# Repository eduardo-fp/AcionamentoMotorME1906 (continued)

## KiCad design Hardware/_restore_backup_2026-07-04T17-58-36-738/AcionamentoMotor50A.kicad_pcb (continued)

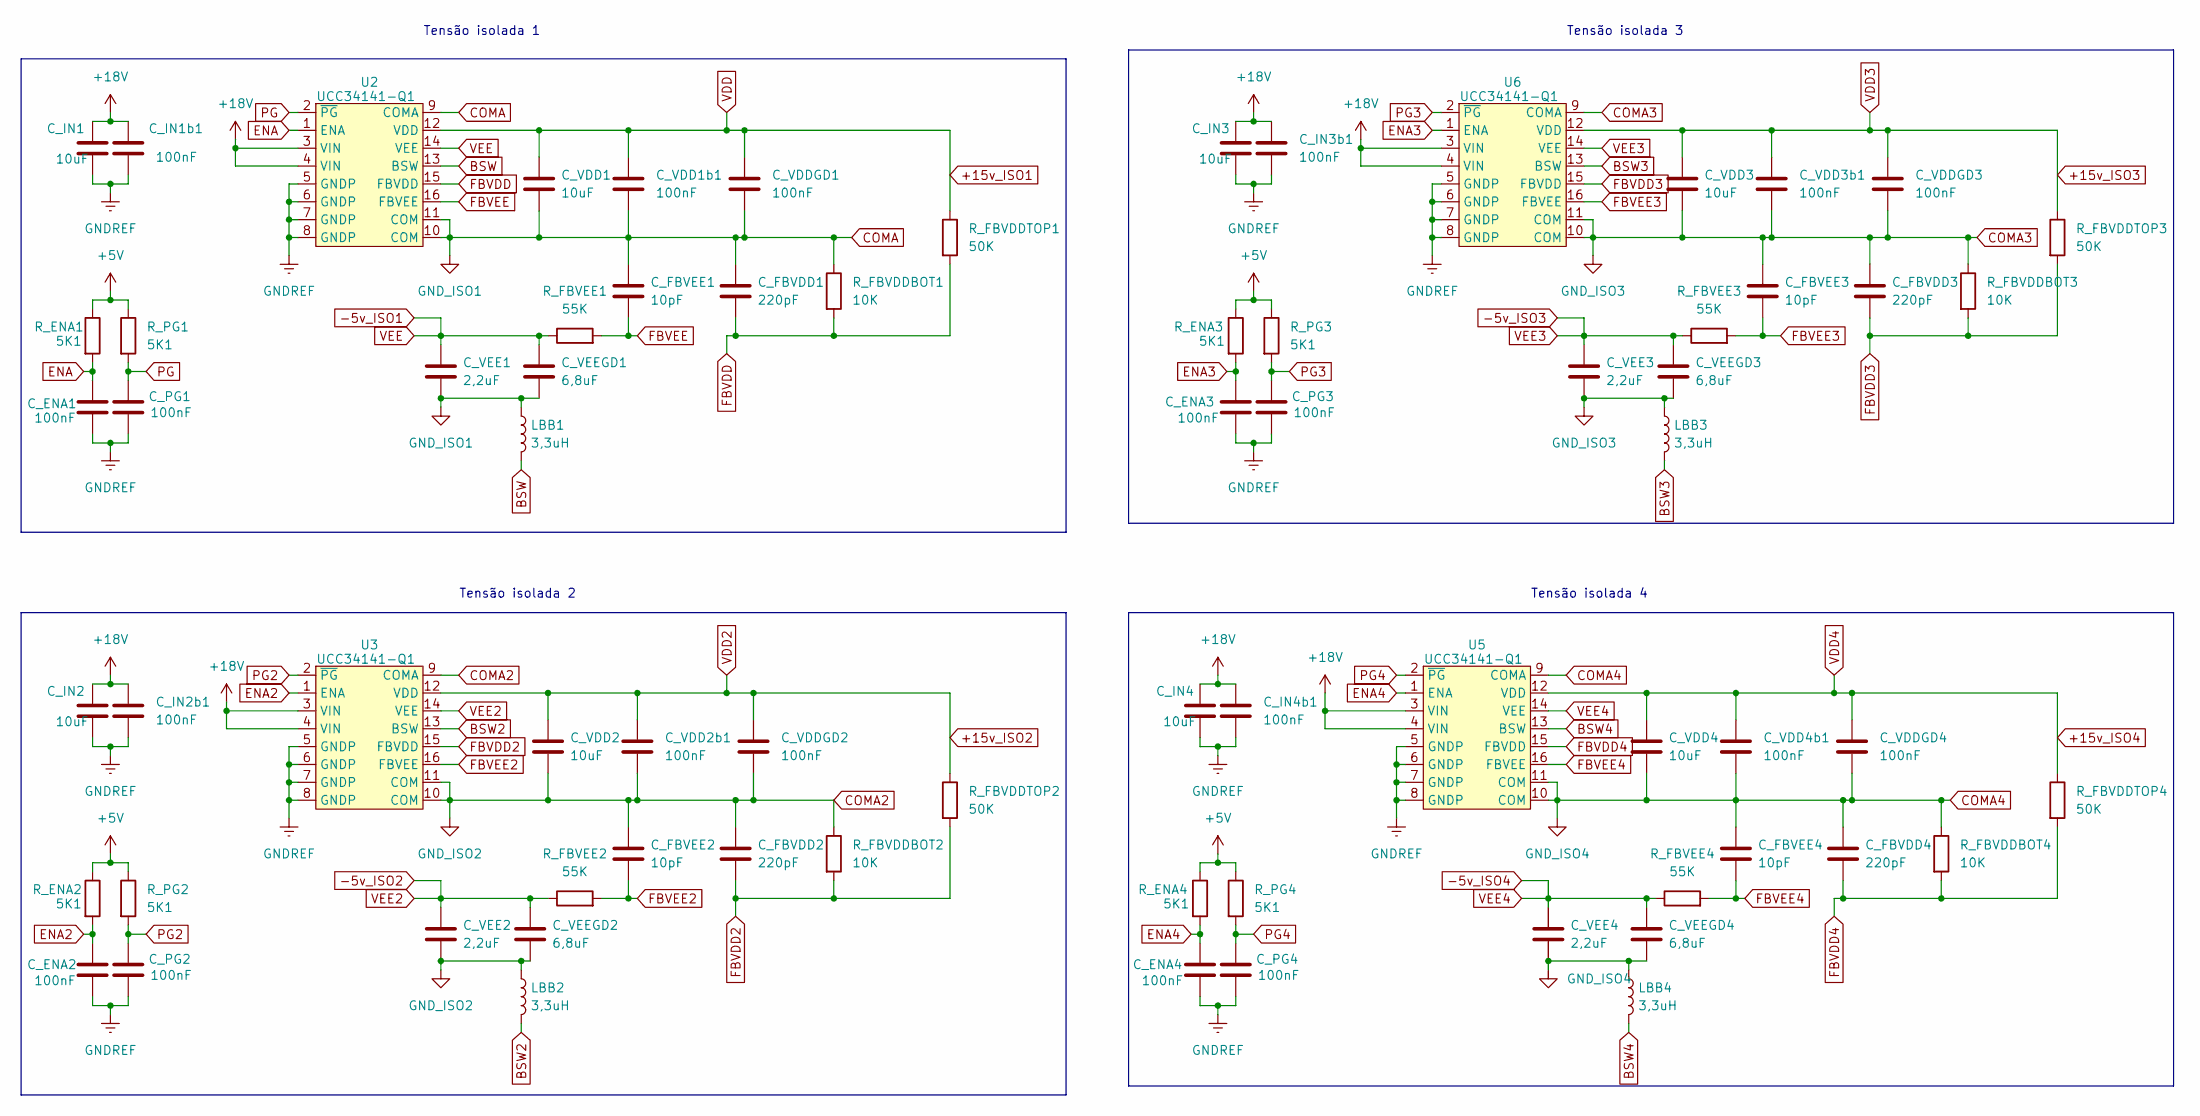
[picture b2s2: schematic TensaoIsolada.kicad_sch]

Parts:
C_ENA1, C_ENA2, C_ENA3, C_ENA4: 100nF; C_0805_2012Metric_Pad1.18x1.45mm_HandSolder
C_FBVDD1, C_FBVDD2, C_FBVDD3, C_FBVDD4: 220pF; C_0805_2012Metric_Pad1.18x1.45mm_HandSolder
C_FBVEE1, C_FBVEE2, C_FBVEE3, C_FBVEE4: 10pF; C_0805_2012Metric_Pad1.18x1.45mm_HandSolder
C_IN1, C_IN2, C_IN3, C_IN4: 10uF; C_0805_2012Metric_Pad1.18x1.45mm_HandSolder
C_IN1b1, C_IN2b1, C_IN3b1, C_IN4b1: 100nF; C_0805_2012Metric_Pad1.18x1.45mm_HandSolder
C_PG1, C_PG2, C_PG3, C_PG4: 100nF; C_0805_2012Metric_Pad1.18x1.45mm_HandSolder
C_VDD1, C_VDD2, C_VDD3, C_VDD4: 10uF; C_0805_2012Metric_Pad1.18x1.45mm_HandSolder
C_VDD1b1, C_VDD2b1, C_VDD3b1, C_VDD4b1: 100nF; C_0805_2012Metric_Pad1.18x1.45mm_HandSolder
C_VDDGD1, C_VDDGD2, C_VDDGD3, C_VDDGD4: 100nF; C_0805_2012Metric_Pad1.18x1.45mm_HandSolder
C_VEE1, C_VEE2, C_VEE3, C_VEE4: 2,2uF; C_0805_2012Metric_Pad1.18x1.45mm_HandSolder
C_VEEGD1, C_VEEGD2, C_VEEGD3, C_VEEGD4: 6,8uF; C_0805_2012Metric_Pad1.18x1.45mm_HandSolder
LBB1, LBB2, LBB3, LBB4: 3,3uH; L_0805_2012Metric_Pad1.05x1.20mm_HandSolder
R_ENA1, R_ENA2, R_ENA3, R_ENA4: 5K1; R_0805_2012Metric_Pad1.20x1.40mm_HandSolder
R_FBVDDBOT1, R_FBVDDBOT2, R_FBVDDBOT3, R_FBVDDBOT4: 10K; R_0805_2012Metric_Pad1.20x1.40mm_HandSolder
R_FBVDDTOP1, R_FBVDDTOP2, R_FBVDDTOP3, R_FBVDDTOP4: 50K; R_0805_2012Metric_Pad1.20x1.40mm_HandSolder
R_FBVEE1, R_FBVEE2, R_FBVEE3, R_FBVEE4: 55K; R_0805_2012Metric_Pad1.20x1.40mm_HandSolder
R_PG1, R_PG2, R_PG3, R_PG4: 5K1; R_0805_2012Metric_Pad1.20x1.40mm_HandSolder
U2, U3, U5, U6: UCC34141-Q1; SSOP-16_4.55x10.63mm_P0.65mm

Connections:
+5V: R_ENA1.1, R_ENA2.1, R_ENA3.1, R_ENA4.1, R_PG1.1, R_PG2.1, R_PG3.1, R_PG4.1; also elsewhere on the board
+15v_ISO1: C_VDD1.1, C_VDD1b1.1, C_VDDGD1.1, R_FBVDDTOP1.1, U2.12 (VDD)
+15v_ISO2: C_VDD2.1, C_VDD2b1.1, C_VDDGD2.1, R_FBVDDTOP2.1, U3.12 (VDD)
+15v_ISO3: C_VDD3.1, C_VDD3b1.1, C_VDDGD3.1, R_FBVDDTOP3.1, U6.12 (VDD)
+15v_ISO4: C_VDD4.1, C_VDD4b1.1, C_VDDGD4.1, R_FBVDDTOP4.1, U5.12 (VDD)
+18V: C_IN1.1, C_IN1b1.1, C_IN2.1, C_IN2b1.1, C_IN3.1, C_IN3b1.1, C_IN4.1, C_IN4b1.1, U2.3 (VIN), U2.4 (VIN), U3.3 (VIN), U3.4 (VIN), U5.3 (VIN), U5.4 (VIN), U6.3 (VIN), U6.4 (VIN); also elsewhere on the board
-5v_ISO1: C_VEE1.1, C_VEEGD1.1, R_FBVEE1.1, U2.14 (VEE)
-5v_ISO2: C_VEE2.1, C_VEEGD2.1, R_FBVEE2.1, U3.14 (VEE)
-5v_ISO3: C_VEE3.1, C_VEEGD3.1, R_FBVEE3.1, U6.14 (VEE)
-5v_ISO4: C_VEE4.1, C_VEEGD4.1, R_FBVEE4.1, U5.14 (VEE)
BAT-: C_ENA1.2, C_ENA2.2, C_ENA3.2, C_ENA4.2, C_IN1.2, C_IN1b1.2, C_IN2.2, C_IN2b1.2, C_IN3.2, C_IN3b1.2, C_IN4.2, C_IN4b1.2, C_PG1.2, C_PG2.2, C_PG3.2, C_PG4.2, U2.5 (GNDP), U2.6 (GNDP), U2.7 (GNDP), U2.8 (GNDP), U3.5 (GNDP), U3.6 (GNDP), U3.7 (GNDP), U3.8 (GNDP), U5.5 (GNDP), U5.6 (GNDP), U5.7 (GNDP), U5.8 (GNDP), U6.5 (GNDP), U6.6 (GNDP), U6.7 (GNDP), U6.8 (GNDP); also elsewhere on the board
BSW: LBB1.2, U2.13 (BSW)
BSW2: LBB2.2, U3.13 (BSW)
BSW3: LBB3.2, U6.13 (BSW)
BSW4: LBB4.2, U5.13 (BSW)
COMA: C_FBVDD1.1, C_FBVEE1.1, C_VDD1.2, C_VDD1b1.2, C_VDDGD1.2, C_VEE1.2, C_VEEGD1.2, LBB1.1, R_FBVDDBOT1.1, U2.9 (COMA), U2.10 (COM), U2.11 (COM)
COMA2: C_FBVDD2.1, C_FBVEE2.1, C_VDD2.2, C_VDD2b1.2, C_VDDGD2.2, C_VEE2.2, C_VEEGD2.2, LBB2.1, R_FBVDDBOT2.1, U3.9 (COMA), U3.10 (COM), U3.11 (COM)
COMA3: C_FBVDD3.1, C_FBVEE3.1, C_VDD3.2, C_VDD3b1.2, C_VDDGD3.2, C_VEE3.2, C_VEEGD3.2, LBB3.1, R_FBVDDBOT3.1, U6.9 (COMA), U6.10 (COM), U6.11 (COM)
COMA4: C_FBVDD4.1, C_FBVEE4.1, C_VDD4.2, C_VDD4b1.2, C_VDDGD4.2, C_VEE4.2, C_VEEGD4.2, LBB4.1, R_FBVDDBOT4.1, U5.9 (COMA), U5.10 (COM), U5.11 (COM)
ENA: C_ENA1.1, R_ENA1.2, U2.1 (ENA)
ENA2: C_ENA2.1, R_ENA2.2, U3.1 (ENA)
ENA3: C_ENA3.1, R_ENA3.2, U6.1 (ENA)
ENA4: C_ENA4.1, R_ENA4.2, U5.1 (ENA)
FBVDD: C_FBVDD1.2, R_FBVDDBOT1.2, R_FBVDDTOP1.2, U2.15 (FBVDD)
FBVDD2: C_FBVDD2.2, R_FBVDDBOT2.2, R_FBVDDTOP2.2, U3.15 (FBVDD)
FBVDD3: C_FBVDD3.2, R_FBVDDBOT3.2, R_FBVDDTOP3.2, U6.15 (FBVDD)
FBVDD4: C_FBVDD4.2, R_FBVDDBOT4.2, R_FBVDDTOP4.2, U5.15 (FBVDD)
FBVEE: C_FBVEE1.2, R_FBVEE1.2, U2.16 (FBVEE)
FBVEE2: C_FBVEE2.2, R_FBVEE2.2, U3.16 (FBVEE)
FBVEE3: C_FBVEE3.2, R_FBVEE3.2, U6.16 (FBVEE)
FBVEE4: C_FBVEE4.2, R_FBVEE4.2, U5.16 (FBVEE)
PG: C_PG1.1, R_PG1.2, U2.2 (~PG)
PG2: C_PG2.1, R_PG2.2, U3.2 (~PG)
PG3: C_PG3.1, R_PG3.2, U6.2 (~PG)
PG4: C_PG4.1, R_PG4.2, U5.2 (~PG)

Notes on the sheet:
Tensão isolada 4
Tensão isolada 2
Tensão isolada 3
Tensão isolada 1

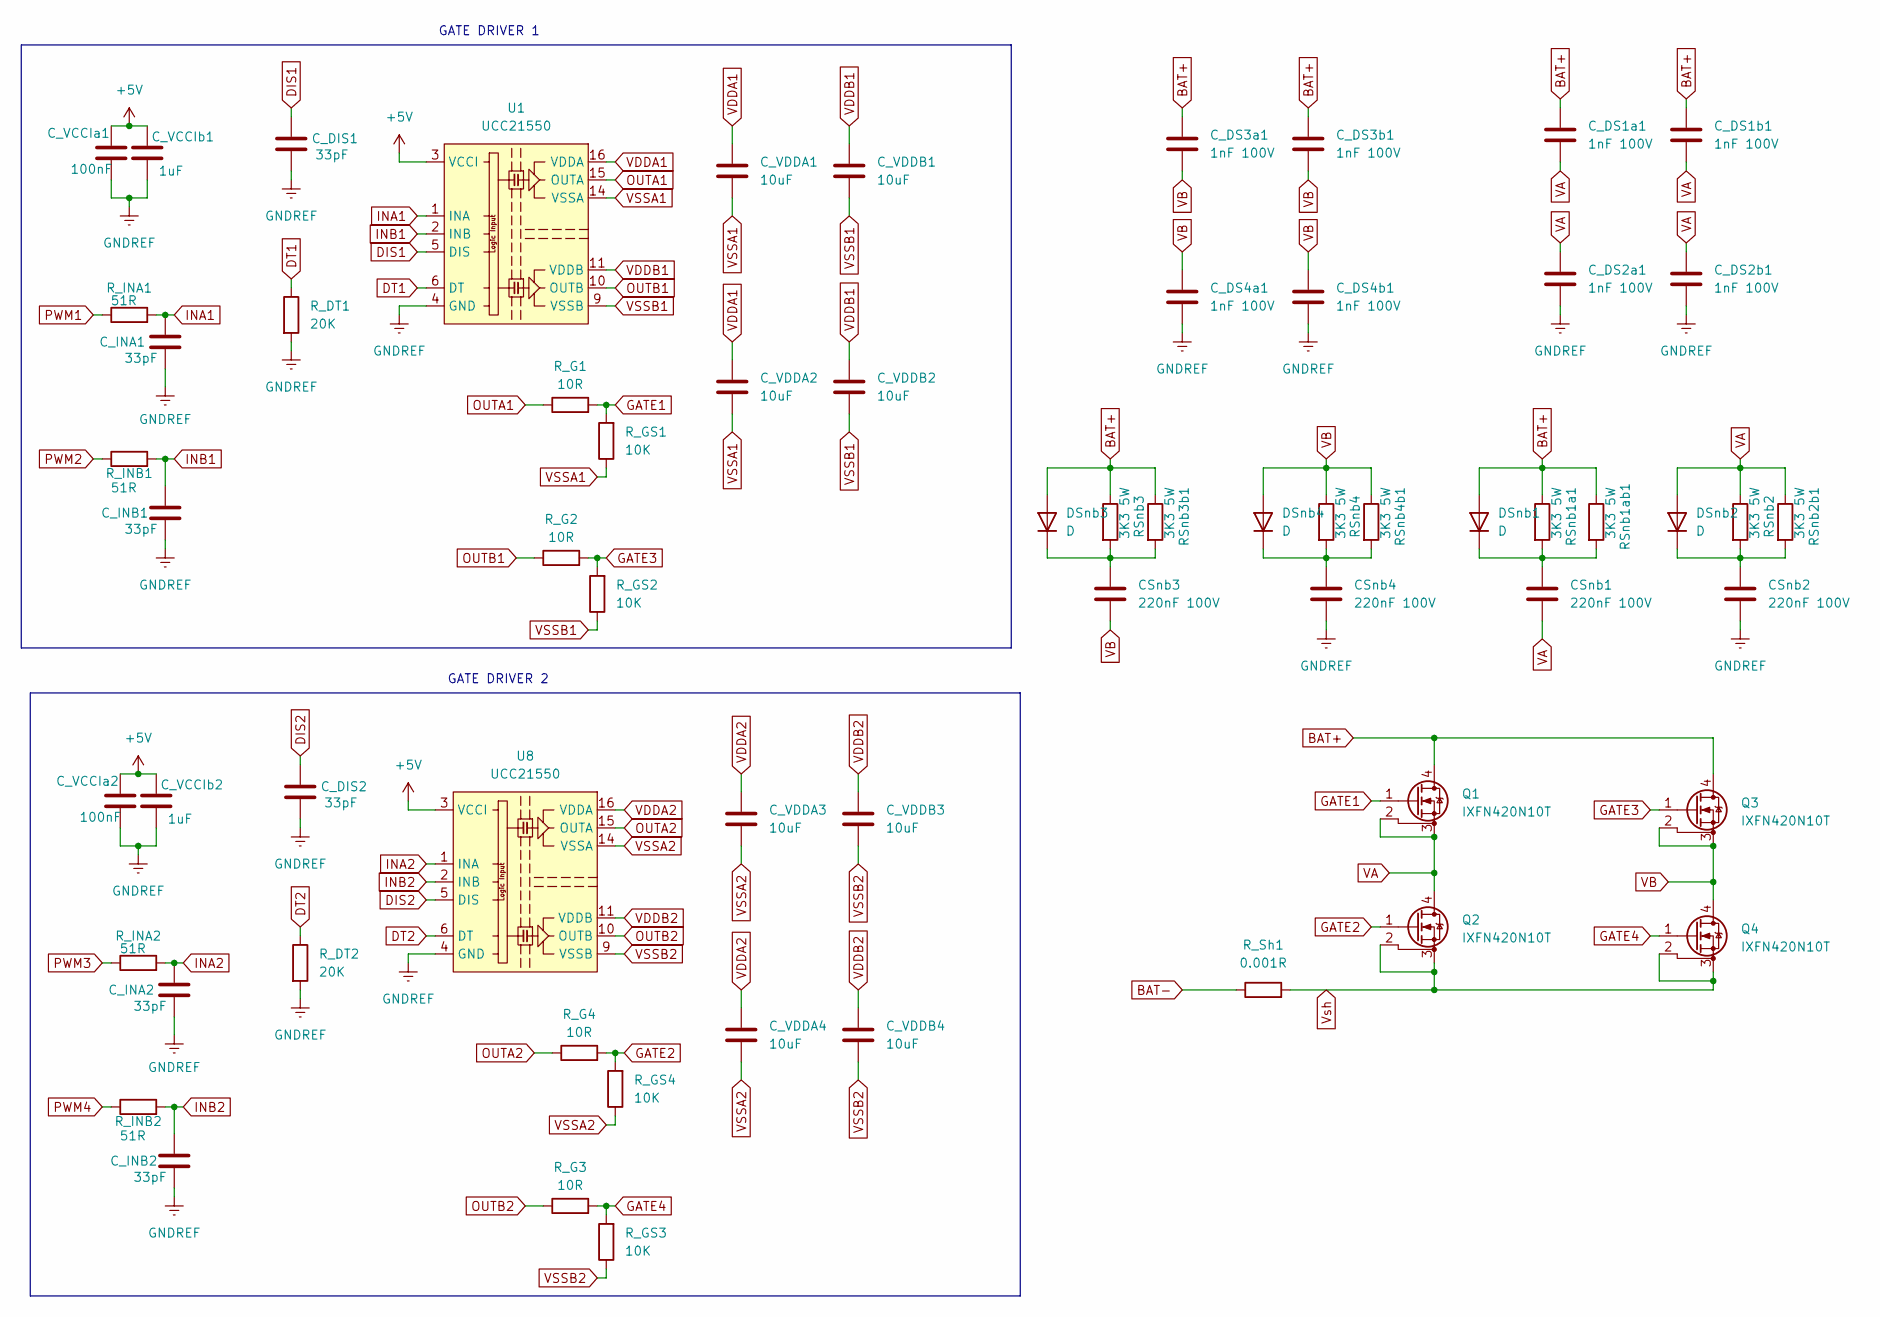
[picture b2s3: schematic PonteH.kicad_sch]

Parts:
CSnb1, CSnb2, CSnb3, CSnb4: 220nF 100V; C_Axial_L5.1mm_D3.1mm_P10.00mm_Horizontal
C_DIS1, C_DIS2: 33pF; C_0805_2012Metric_Pad1.18x1.45mm_HandSolder
C_DS1a1, C_DS1b1, C_DS2a1, C_DS2b1, C_DS3a1, C_DS3b1, C_DS4a1, C_DS4b1: 1nF 100V; C_0805_2012Metric_Pad1.18x1.45mm_HandSolder
C_INA1, C_INA2: 33pF; C_0805_2012Metric_Pad1.18x1.45mm_HandSolder
C_INB1, C_INB2: 33pF; C_0805_2012Metric_Pad1.18x1.45mm_HandSolder
C_VCCI​a1, C_VCCI​a2: 100nF; C_0805_2012Metric_Pad1.18x1.45mm_HandSolder
C_VCCI​b1, C_VCCI​b2: 1uF; C_0805_2012Metric_Pad1.18x1.45mm_HandSolder
C_VDDA1, C_VDDA2, C_VDDA3, C_VDDA4: 10uF; C_0805_2012Metric_Pad1.18x1.45mm_HandSolder
C_VDDB1, C_VDDB2, C_VDDB3, C_VDDB4: 10uF; C_0805_2012Metric_Pad1.18x1.45mm_HandSolder
DSnb1, DSnb2, DSnb3, DSnb4: D; D_SMA_Handsoldering
Q1, Q2, Q3, Q4: IXFN420N10T; SOT-227
RSnb1a1, RSnb1ab1, RSnb2, RSnb2b1, RSnb3, RSnb3b1, RSnb4, RSnb4b1: 3K3 5W; R_Axial_Power_L25.0mm_W9.0mm_P27.94mm
R_DT1, R_DT2: 20K; R_0805_2012Metric_Pad1.20x1.40mm_HandSolder
R_G1, R_G2, R_G3, R_G4: 10R; R_0805_2012Metric_Pad1.20x1.40mm_HandSolder
R_GS1, R_GS2, R_GS3, R_GS4: 10K; R_0805_2012Metric_Pad1.20x1.40mm_HandSolder
R_INA1, R_INA2: 51R; R_0805_2012Metric_Pad1.20x1.40mm_HandSolder
R_INB1, R_INB2: 51R; R_0805_2012Metric_Pad1.20x1.40mm_HandSolder
R_Sh1: 0.001R; R_Axial_Power_L20.0mm_W6.4mm_P25.40mm
U1, U8: UCC21550; SOIC-16W_7.5x10.3mm_P1.27mm

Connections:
+5V: C_VCCI​a1.1, C_VCCI​a2.1, C_VCCI​b1.1, C_VCCI​b2.1, U1.3 (VCCI), U1.8 (VCCI), U8.3 (VCCI), U8.8 (VCCI); also elsewhere on the board
BAT+: C_DS1a1.1, C_DS1b1.1, C_DS3a1.1, C_DS3b1.1, DSnb1.2 (A), DSnb3.2 (A), Q1.4 (D), Q3.4 (D), RSnb1a1.1, RSnb1ab1.1, RSnb3.1, RSnb3b1.1; also elsewhere on the board
BAT-: CSnb2.2, CSnb4.2, C_DIS1.2, C_DIS2.2, C_DS2a1.2, C_DS2b1.2, C_DS4a1.2, C_DS4b1.2, C_INA1.2, C_INA2.2, C_INB1.2, C_INB2.2, C_VCCI​a1.2, C_VCCI​a2.2, C_VCCI​b1.2, C_VCCI​b2.2, R_DT1.2, R_DT2.2, R_Sh1.1, U1.4 (GND), U8.4 (GND); also elsewhere on the board
DIS1: C_DIS1.1, C_DIS2.1, U1.5 (DIS), U8.5 (DIS); also elsewhere on the board
DT1: R_DT1.1, U1.6 (DT)
DT2: R_DT2.1, U8.6 (DT)
GATE1: Q1.1 (G), R_G1.2, R_GS1.2
GATE4: Q4.1 (G), R_G3.2, R_GS3.2
INA1: C_INA1.1, R_INA1.2, U1.1 (INA)
INA2: C_INA2.1, R_INA2.2, U8.1 (INA)
INB1: C_INB1.1, R_INB1.2, U1.2 (INB)
INB2: C_INB2.1, R_INB2.2, U8.2 (INB)
unnamed: CSnb1.1, DSnb1.1 (K), RSnb1a1.2, RSnb1ab1.2
unnamed: CSnb2.1, DSnb2.1 (K), RSnb2.2, RSnb2b1.2
unnamed: CSnb3.1, DSnb3.1 (K), RSnb3.2, RSnb3b1.2
unnamed: CSnb4.1, DSnb4.1 (K), RSnb4.2, RSnb4b1.2
OUTA1: R_G1.1, U1.15 (OUTA)
OUTA2: R_G4.1, U8.15 (OUTA)
OUTB1: R_G2.1, U1.10 (OUTB)
OUTB2: R_G3.1, U8.10 (OUTB)
PWM1: R_INA1.1; also elsewhere on the board
PWM2: R_INB1.1; also elsewhere on the board
PWM3: R_INA2.1; also elsewhere on the board
PWM4: R_INB2.1; also elsewhere on the board
VA: CSnb1.2, C_DS1a1.2, C_DS1b1.2, C_DS2a1.1, C_DS2b1.1, DSnb2.2 (A), Q1.2 (DS), Q1.3 (S), Q2.4 (D), RSnb2.1, RSnb2b1.1
VB: CSnb3.2, C_DS3a1.2, C_DS3b1.2, C_DS4a1.1, C_DS4b1.1, DSnb4.2 (A), Q3.2 (DS), Q3.3 (S), Q4.4 (D), RSnb4.1, RSnb4b1.1
VDDA1: C_VDDA1.1, C_VDDA2.1, U1.16 (VDDA)
VDDA2: C_VDDA3.1, C_VDDA4.1, U8.16 (VDDA)
VDDB1: C_VDDB1.1, C_VDDB2.1, U1.11 (VDDB)
VDDB2: C_VDDB3.1, C_VDDB4.1, U8.11 (VDDB)
VSSA1: C_VDDA1.2, C_VDDA2.2, R_GS1.1, U1.14 (VSSA)
VSSA2: C_VDDA3.2, C_VDDA4.2, R_GS4.1, U8.14 (VSSA)
VSSB1: C_VDDB1.2, C_VDDB2.2, R_GS2.1, U1.9 (VSSB)
VSSB2: C_VDDB3.2, C_VDDB4.2, R_GS3.1, U8.9 (VSSB)
Vsh: Q2.2 (DS), Q2.3 (S), Q4.2 (DS), Q4.3 (S), R_Sh1.2; also elsewhere on the board

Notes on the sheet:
GATE DRIVER 1
GATE DRIVER 2

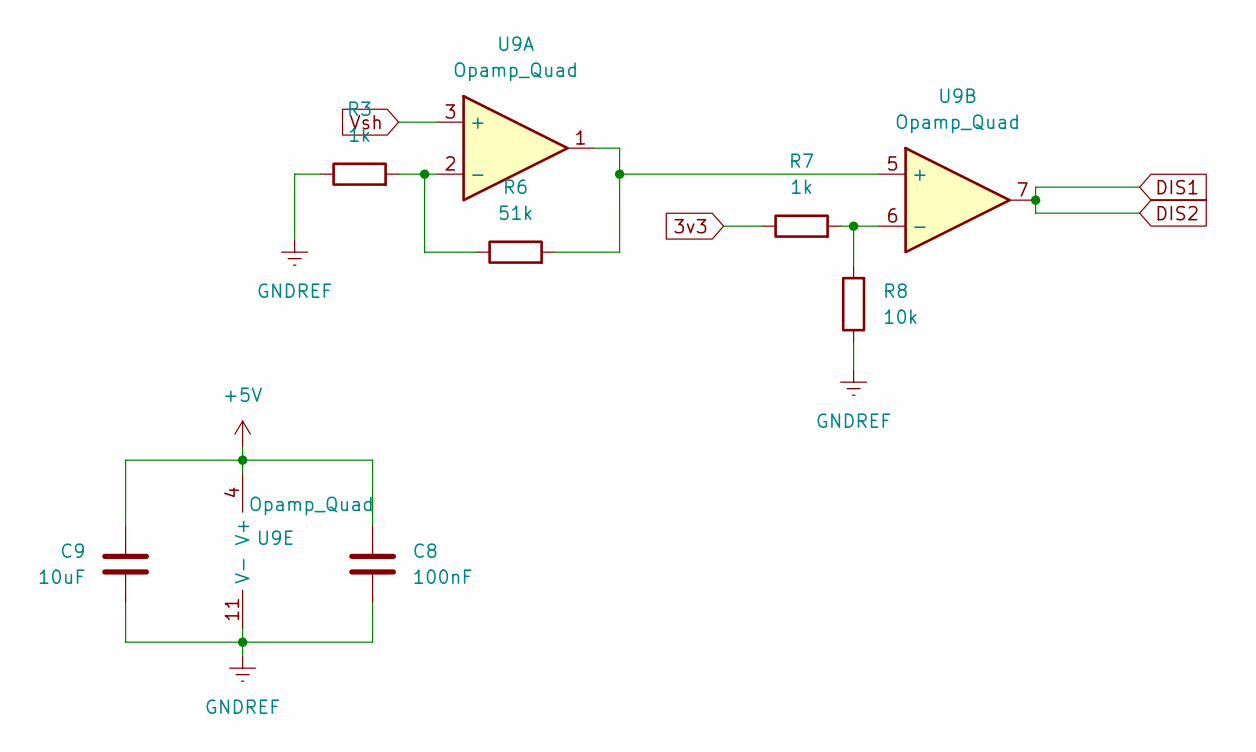
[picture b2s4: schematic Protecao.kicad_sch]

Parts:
C8: 100nF; C_0805_2012Metric_Pad1.18x1.45mm_HandSolder
C9: 10uF; C_0805_2012Metric_Pad1.18x1.45mm_HandSolder
R3, R7: 1k; R_0805_2012Metric_Pad1.20x1.40mm_HandSolder
R6: 51k; R_0805_2012Metric_Pad1.20x1.40mm_HandSolder
R8: 10k; R_0805_2012Metric_Pad1.20x1.40mm_HandSolder
U9: Opamp_Quad; SOIC-14_3.9x8.7mm_P1.27mm

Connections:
3v3: R7.1; also elsewhere on the board
+5V: C8.1, C9.1, U9.4 (V+); also elsewhere on the board
BAT-: C8.2, C9.2, R3.1, R8.1, U9.11 (V-); also elsewhere on the board
DIS1: U9.7; also elsewhere on the board
unnamed: R3.2, R6.1, U9.2 (-)
unnamed: R6.2, U9.1, U9.5 (+)
unnamed: R7.2, R8.2, U9.6 (-)
Vsh: U9.3 (+); also elsewhere on the board

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
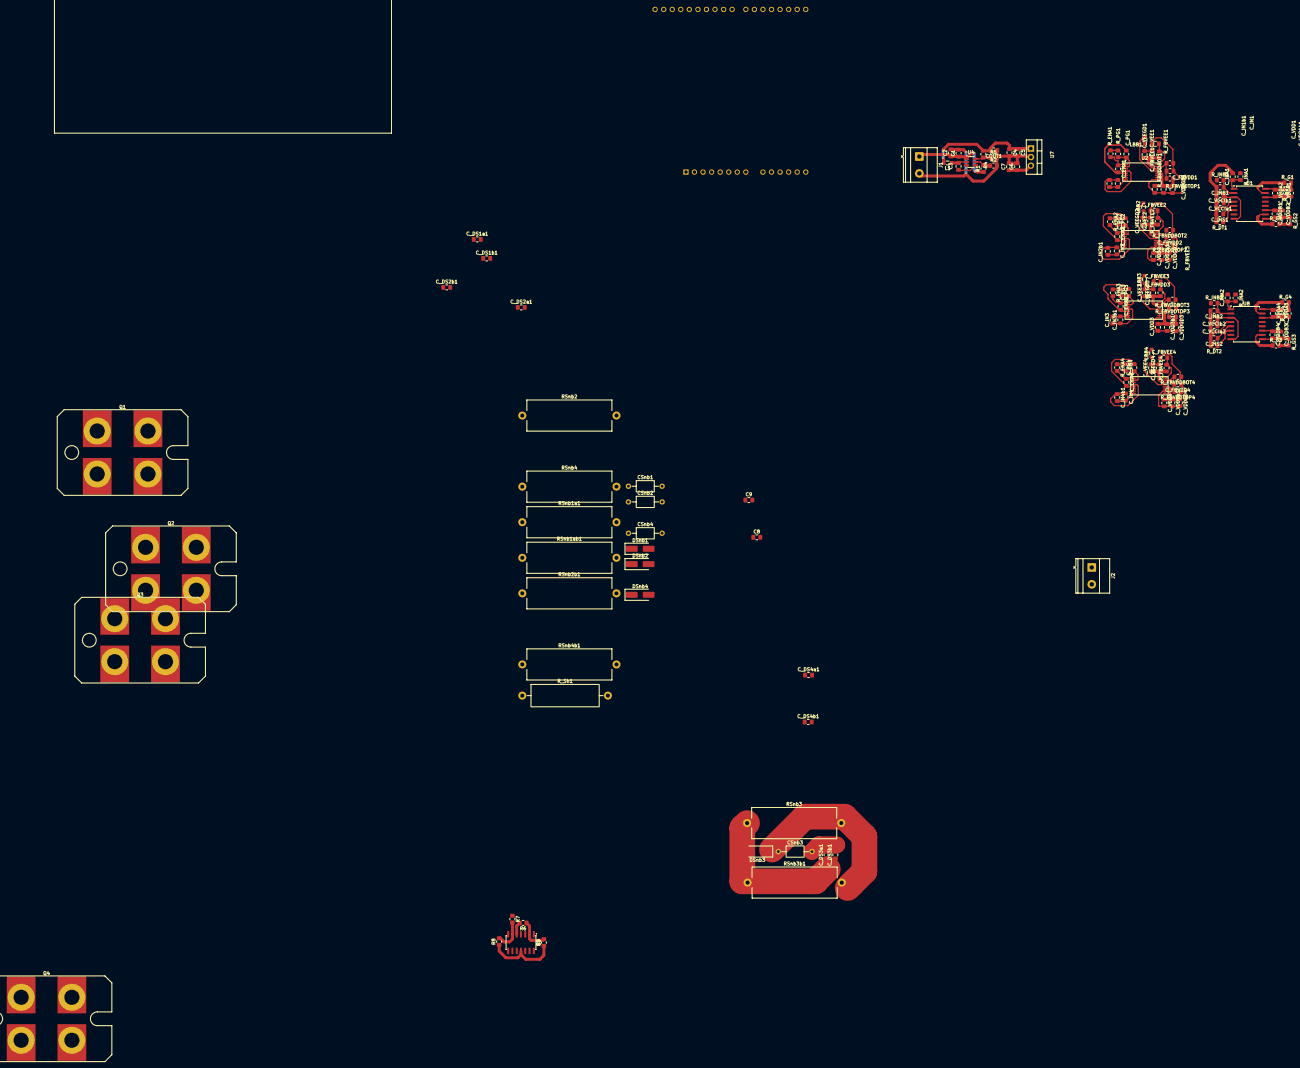
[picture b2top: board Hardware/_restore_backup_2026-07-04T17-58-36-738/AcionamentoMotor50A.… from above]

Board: 2 copper layers, 161 parts (1 on the bottom side), 79 nets.

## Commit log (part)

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2026-06-18 2026-06-18
    Commit da base do projeto
2026-06-18 2026_06_18
    Esquemático atualizado
    Foram colocados os snubbers, capacitores para controlar o tempo de subida (CDS) e capacitores para controlar o tempo em que o MOSFET abre e fecha (CGS)
    Falta calcular os snubbers e ajustar os valores dos capacitores
2026-06-25 2026_06_25
    adicionado o circuito para o MOSFET abrir mais rápido que ela fecha
2026-06-25 2026_06_25
    Esquemático finalizado.
    Footprints corrigidos
